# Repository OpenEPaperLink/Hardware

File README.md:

Hardware files for the OpenEpaperLink project

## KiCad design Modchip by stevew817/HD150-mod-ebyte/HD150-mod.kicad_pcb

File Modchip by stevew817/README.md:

# OEPL hardware modchip for non-flashable devices, by stevew817
License: [CERN-OHL-W-2.0](https://choosealicense.com/licenses/cern-ohl-w-2.0/)

## Introduction
This is sample hardware for modding an electronic shelf label such that it supports running OpenEpaperLink (OEPL) compatible firmware. A 'brain transplant', if you will.

| :warning: WARNING                                               |
|:----------------------------------------------------------------|
| The pinout as indicated on the v2 PCB silkscreen is not the same pinout as implemented in the firmware. See the mod isntructions section below for the correct wiring. |

## Hardware
The modchip originated from a mod of a Pricer HD150 electronic shelf label, which is commonly available on eBay. These are nicely sized, at 5.83" diagonal and a 640x480 resolution. The display inside is a red/black/white eInk display made by a company called 'Good Display' ([GDEW0583Z83](https://www.good-display.com/product/242.html)). The shelf label is interesting as it seems to be in relatively steady supply, and inside it comes with a carrier PCB and injection-molded enclosure with space to spare for an invisible hardware mod.

The stock shelf label is infrared-based, and the protocol has been analyzed by other folks before me. However, for supporting OpenEpaperLink we need 2.4GHz IEEE 802.15.4-based connectivity. Thus, the modchip.

I have spent hours trying to reverse the PCB and firmware running on the chip, ending up having to build a live-surgery setup considering the stock firmware for these is in RAM. That means that when you remove the batteries, the firmware is gone. Yay. The end result is a functional hardware mod with a workable understanding of how to drive the display, which (bonus points!) fits inside the original enclosure after cutting out some plastic supports on the inside. It even supports a rechargeable battery inside the case!

As pictures say more than a thousand words, here you go:

KiCAD source files for the 'modchip' are provided in the `HD150-mod-ebyte` folder. Feel free to remix or use as-is.

### Component list for mod
- LiPo battery which fits in the enclosure space, with built-in undervoltage protection. I used [these](https://www.kjell.com/no/produkter/elektro-og-verktoy/arduino/arduino-tilbehor/luxorparts-li-po-batteri-37-v-med-kontakt-1200-mah-p87924) but have no idea where they are sourced from. A Google search would indicate PKCell. Indicated dimension 63x36x4,7 mm. The same marking code can be found on [Adafruit's battery](https://www.adafruit.com/product/258).
- Assembled PCB ([BOM](./BOM.csv))
  - Notes about the BOM:
    - Choose either a micro-USB connector or a JST-PH connector for the power input (i.e. choose either J2 or J4). The JST-PH footprint is also good for soldering a cable with a custom charging contact on to if desired.
    - JP1 is for testing purposes only. The debug UART doesn't support input, it only prints output, so the RX signal goes unused and PA06 is exposed as a solder pad for future use.
    - Either mount the mini-simplicity connector on J3 for flashing the chip with a Silicon Labs WSTK, or use a tag-connect Cortex cable (and a debug probe of your choice which supports EFR32BG22) on footprint J5.
  - Note about the [module](https://www.cdebyte.com/products/E104-BT53A1): can be sourced from [AliExpress in a 10-pack](https://www.aliexpress.com/item/4001276005199.html) for less than $2/pc.
- Electrical wire

Tools:
- Soldering iron / hot plate
- Hot glue
- Scalpel
- Side-cutting pliers

### Mod instructions for HD150
More pictures...

:warning: The pinout as shown here is NOT the same as implemented in firmware. The correct wiring for the v2 PCB with v3 and above firmware is as follows:

| Function | HD150 solder point | ESL modchip v2 PCB solder pad | ESL modchip v3 PCB solder pad |
|----------|--------------------|-------------------------------|-------------------------------|
| MOSI     | TP24               | SDIO (PA4)                    | PA4                           |
| SCLK     | TP28               | SCLK (PB0)                    | PB0                           |
| nCS      | TP42               | CS_M (PA0)                    | PA0                           |
| nRST     | TP40               | BUSY (PD0)                    | PD0                           |
| BUSY     | TP41               | RST (PB2)                     | PB2                           |
| D/C      | TP43               | CS_S (PC1 - this is a typo on v2 silkscreen, the pad is actually connected to the MCU pin PD1) | PD1                           |
| DSP_EN   | See image          | PA6                           | PA6                           |
| VCC      | TP2                | VCC                           | VCC                           |
| GND      | Any ground pad     | GND                           | GND                           |
| (BTN)    | Button lower left  | D/C (PB1) (optional)          | PB1                           |

Image as reference for cutting the correct traces and finding the relevant testpoints, does not show the above pinout!

Removing elements from the back casing to make room for the mod:

In writing:
- Open the HD150 casing using a thin metal opening tool. It has clips all around the case. You could use a knife, but I fully recommend using something less prone to cause injury, such as [iFixit's Jimmy](https://www.ifixit.com/products/jimmy).
- Remove the carrier PCB from the housing. This is done best through releasing the 2 gripper hooks in one corner first, and then the other corner.
- Cut the traces along the red line as indicated on the picture above.
- Affix the modchip with a dot of hot glue in the location as shown in the picture above.
- Wire the testpoints to the pads on the modchip as indicated in the picture above.
- Affix the wires with some hot glue.
- On the back plastic housing, remove the original battery modules and cut away the enclosure walls in the places where the wires and the battery pack would go. Side-cutting pliers are the tool of choice here. See the picture above for visual instructions.
- Cut an opening in the back housing for the modchip's programming and charging connectors if you want to be able to reflash without having to disassemble the housing again. Using a scalpel works, but melting a hole would probably be easier/faster. Again, see the picture for visual instructions.
- Reinstall the display PCB into the back housing.
- Click the front housing frame in place again.

## Firmware
The firmware is built as part of the EFR32xG22 implementation of OEPL, residing in a [separate repository](https://github.com/OpenEPaperLink/Tag_FW_EFR32xG22). Note that if you want the modchip to support a different display than the HD150/GDEW0583Z83, you'll need to either implement support for that yourself (and please send a PR!), or open an issue with your request (not guaranteed to be followed up on, depends on available time and access to hardware).

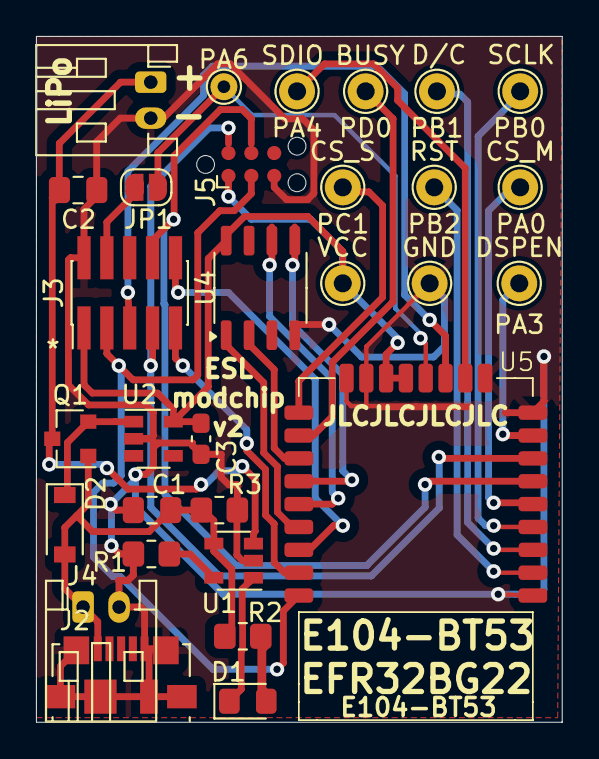
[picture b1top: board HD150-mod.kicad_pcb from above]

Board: 2 copper layers, 29.2 x 38.1 mm, 30 parts (0 on the bottom side), 28 nets.

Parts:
BUSY: TestPoint; TestPoint_THTPad_D2.0mm_Drill1.0mm
C1, C2: 4.7u; C_0805_2012Metric_Pad1.18x1.45mm_HandSolder
C3: 100n; C_0603_1608Metric_Pad1.08x0.95mm_HandSolder
CS_M: TestPoint; TestPoint_THTPad_D2.0mm_Drill1.0mm
CS_S: TestPoint; TestPoint_THTPad_D2.0mm_Drill1.0mm
D1: LED; LED_0805_2012Metric_Pad1.15x1.40mm_HandSolder
D2: SBR80520; D_SOD-123
D/C: TestPoint; TestPoint_THTPad_D2.0mm_Drill1.0mm
DSPEN: TestPoint; TestPoint_THTPad_D2.0mm_Drill1.0mm
GND: TestPoint; TestPoint_THTPad_D2.0mm_Drill1.0mm
J1: BAT; JST_PH_S2B-PH-K_1x02_P2.00mm_Horizontal
J2: USB_B_Micro; USB_Micro-B_Molex_47346-0001
J3: Mini-Simplicity; PinHeader_2x05_P1.27mm_Vertical_SMD
J4: PWR_IN; JST_PH_S2B-PH-K_1x02_P2.00mm_Horizontal
J5: Conn_ARM_SWD_TagConnect_TC2030-NL; Tag-Connect_TC2030-IDC-NL_2x03_P1.27mm_Vertical
JP1: SolderJumper_2_Open; SolderJumper-2_P1.3mm_Open_RoundedPad1.0x1.5mm
PA6: TestPoint; TestPoint_THTPad_D1.5mm_Drill0.7mm
Q1: NVR1P02; SOT-23
R1: 2k2; R_0805_2012Metric_Pad1.20x1.40mm_HandSolder
R2: 680R; R_0805_2012Metric_Pad1.20x1.40mm_HandSolder
R3: 6k; R_0805_2012Metric_Pad1.20x1.40mm_HandSolder
RST: TestPoint; TestPoint_THTPad_D2.0mm_Drill1.0mm
SCLK: TestPoint; TestPoint_THTPad_D2.0mm_Drill1.0mm
SDIO: TestPoint; TestPoint_THTPad_D2.0mm_Drill1.0mm
U1: MCP73831; SOT-23-5
U2: TPS70936; SOT-23-5
U4: MX25R1635FM1xx0; SOP-8_3.9x4.9mm_P1.27mm
U5: E104-BT53
VCC: TestPoint; TestPoint_THTPad_D2.0mm_Drill1.0mm

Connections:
+5V: C1.1, D2.2 (A), J2.1 (VBUS), J4.1, Q1.1 (G), R2.1, R3.1, U1.4 (VDD)
+BATT: C2.1, J1.1, Q1.3 (D), U1.3 (VBAT)
F_CS: U4.1 (~CS), U5.23 (PC03)
F_MISO: U4.2 (SO/SIO1), U5.20 (PC00)
F_MOSI: U4.5 (SI/SIO0), U5.21 (PC01)
F_SCK: U4.6 (SCLK), U5.22 (PC02)
GND: C1.2, C2.2, C3.2, GND.1, J1.2, J2.5 (GND), J2.6 (Shield), J3.2, J4.2, J5.5 (GND), R1.2, R3.2, U1.2 (VSS), U2.2 (GND), U4.4 (GND), U5.1 (GND), U5.9 (GND), U5.10 (GND), U5.16 (GND), U5.17 (GND)
unnamed: D1.2 (A), R2.2
unnamed: D1.1 (K), U1.1 (STAT)
unnamed: D2.1 (K), Q1.2 (S), U2.1 (IN)
unnamed: J3.4, JP1.1 (A)
unnamed: R1.1, U1.5 (PROG)
unnamed: CS_M.1, U5.5 (PA00)
unnamed: DSPEN.1, U5.8 (PA03)
unnamed: SDIO.1, U5.11 (PA04)
unnamed: SCLK.1, U5.4 (PB00)
unnamed: D/C.1, U5.3 (PB01)
unnamed: RST.1, U5.2 (PB02)
unnamed: BUSY.1, U5.19 (PD00)
unnamed: CS_S.1, U5.18 (PD01)
PTI_DATA: J3.10, U5.24 (PC04)
PTI_FRAME: J3.9, U5.25 (PC05)
SWCLK: J3.8, J5.4 (SWCLK), U5.6 (PA01)
SWDIO: J3.7, J5.2 (SWDIO), U5.7 (PA02)
VCC: C3.1, J3.1, J5.1 (VCC), U2.5 (OUT), U4.8 (VCC), U5.14 (VCC), U5.15 (VCC), VCC.1
VCOM_RX: JP1.2 (B), PA6.1, U5.13 (PA06)
VCOM_TX: J3.5, U5.12 (PA05)
nRST: J3.3, J5.3 (~RESET), U5.26 (nRST)

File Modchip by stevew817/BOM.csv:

"Reference","Value","Datasheet","Footprint","Qty","DNP"
"C1,C2","4.7u","~","Capacitor_SMD:C_0805_2012Metric_Pad1.18x1.45mm_HandSolder","2",""
"C3","100n","~","Capacitor_SMD:C_0603_1608Metric_Pad1.08x0.95mm_HandSolder","1",""
"D1","LED","~","LED_SMD:LED_0805_2012Metric_Pad1.15x1.40mm_HandSolder","1",""
"D2","SBR80520","~","Diode_SMD:D_SOD-123","1",""
"J1","BAT","~","Connector_JST:JST_PH_S2B-PH-K_1x02_P2.00mm_Horizontal","1",""
"J2","USB_B_Micro","~","Connector_USB:USB_Micro-B_Molex_47346-0001","1",""
"J3","Mini-Simplicity","~","Connector_PinHeader_1.27mm:PinHeader_2x05_P1.27mm_Vertical_SMD","1",""
"J4","PWR_IN","~","Connector_JST:JST_PH_S2B-PH-K_1x02_P2.00mm_Horizontal","1",""
"Q1","NVR1P02","http://www.vishay.com/docs/70209/70209.pdf","Package_TO_SOT_SMD:SOT-23","1",""
"R1","2k2","~","Resistor_SMD:R_0805_2012Metric_Pad1.20x1.40mm_HandSolder","1",""
"R2","680R","~","Resistor_SMD:R_0805_2012Metric_Pad1.20x1.40mm_HandSolder","1",""
"R3","6k","~","Resistor_SMD:R_0805_2012Metric_Pad1.20x1.40mm_HandSolder","1",""
"U1","MCP73831","http://ww1.microchip.com/downloads/en/DeviceDoc/20001984g.pdf","Package_TO_SOT_SMD:SOT-23-5","1",""
"U2","TPS70936","https://www.ti.com/lit/ds/symlink/tps7a05.pdf","Package_TO_SOT_SMD:SOT-23-5","1",""
"U4","MX25R1635FM1xx0","http://www.macronix.com/Lists/Datasheet/Attachments/7534/MX2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,%20Wide%20Range,%2032Mb,%20v1.6.pdf","Package_SO:SOP-8_3.9x4.9mm_P1.27mm","1",""
"U5","E104-BT53","https://www.cdebyte.com/pdf-down.aspx?id=1492","RF_Module:E104-BT53","1",""

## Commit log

2024-06-18 EFR32BG22 'modchip' hardware files
2024-06-18 [modchip] Add explanatory note about connectors on the PCB.
2024-06-25 Update with link to EFR32xG22 firmware project
2024-07-16 Note correct pinout for HD150 modchip
2024-10-03 move files
2024-10-03 add new files
2024-10-19 Hanshow Nebular wall mount slim
    Using the space below the battery & electronic compartment, this wall mount is as slim as possible while maintaining a place for a screw.
    Designed for the Nebular-200-N using the same footprint, also fits the Nebular-350-N.
2024-10-28 Added 1.4 gerber files
    Including pick and place csv
2024-11-05 Added NanoTLSR AP Case
2024-12-09 Added print settings for Picksmart mounting Hardware
2024-12-09 Added Picksmart 2.9 and 4.2 Holders
2024-12-17 Added YellowAP Parts image
2024-12-18 Added Hanshow Nebular 200-N Lasercut Jig
2024-12-18 Added Hanshow Nebular 350-N Lasercut Jig
2024-12-19 Added Solum Newton Lite 1.6 (Lasercut) Jig
2024-12-20 Added Solum Newton M3 4.3 (Lasercut) Jig
2025-01-10 Added 3.5" Cover and Stand stl
2025-01-16 Added atc1441's Gerber_4InchAP_PCB.zip.
2025-01-17 Added 7_5_Cover
2025-02-01 Added Fully 3D Printable Case and Stand for the 9.7" DIY
2025-02-05 Added YellowAP update
2025-02-10 Added chroma29_C_jig_v1.0.stl by Discord user T0b!
2025-02-21 Add Spaghetti AP PCB
2025-03-17 Added 3d printable stand and holder for Chroma29 tag by Discord user MaZZly
2025-03-31 Added 4inchC6_AP
2025-04-01 Added 3D Printable Backplane for 4inchAP
2025-04-15 Added 3D Printable 5.81" Case
2025-06-03 Added Spaghetti AP Skadis lid
2025-07-07 Fix typo for image in README.md
2026-05-30 Fix image tag for Seperate Yellow AP in README
2026-06-24 Added M3 7.5 and 8.2 Holder and Stand by Sebastian
